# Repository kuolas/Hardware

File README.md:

# Hardware

Every folder is a board originally designed for a particular project but are generic enough to be used in other projects.

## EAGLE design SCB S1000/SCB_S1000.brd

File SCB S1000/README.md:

# SCB S1000

Stepper Controller Board based on L297 and L296.

These file were created using EAGLE 5.10

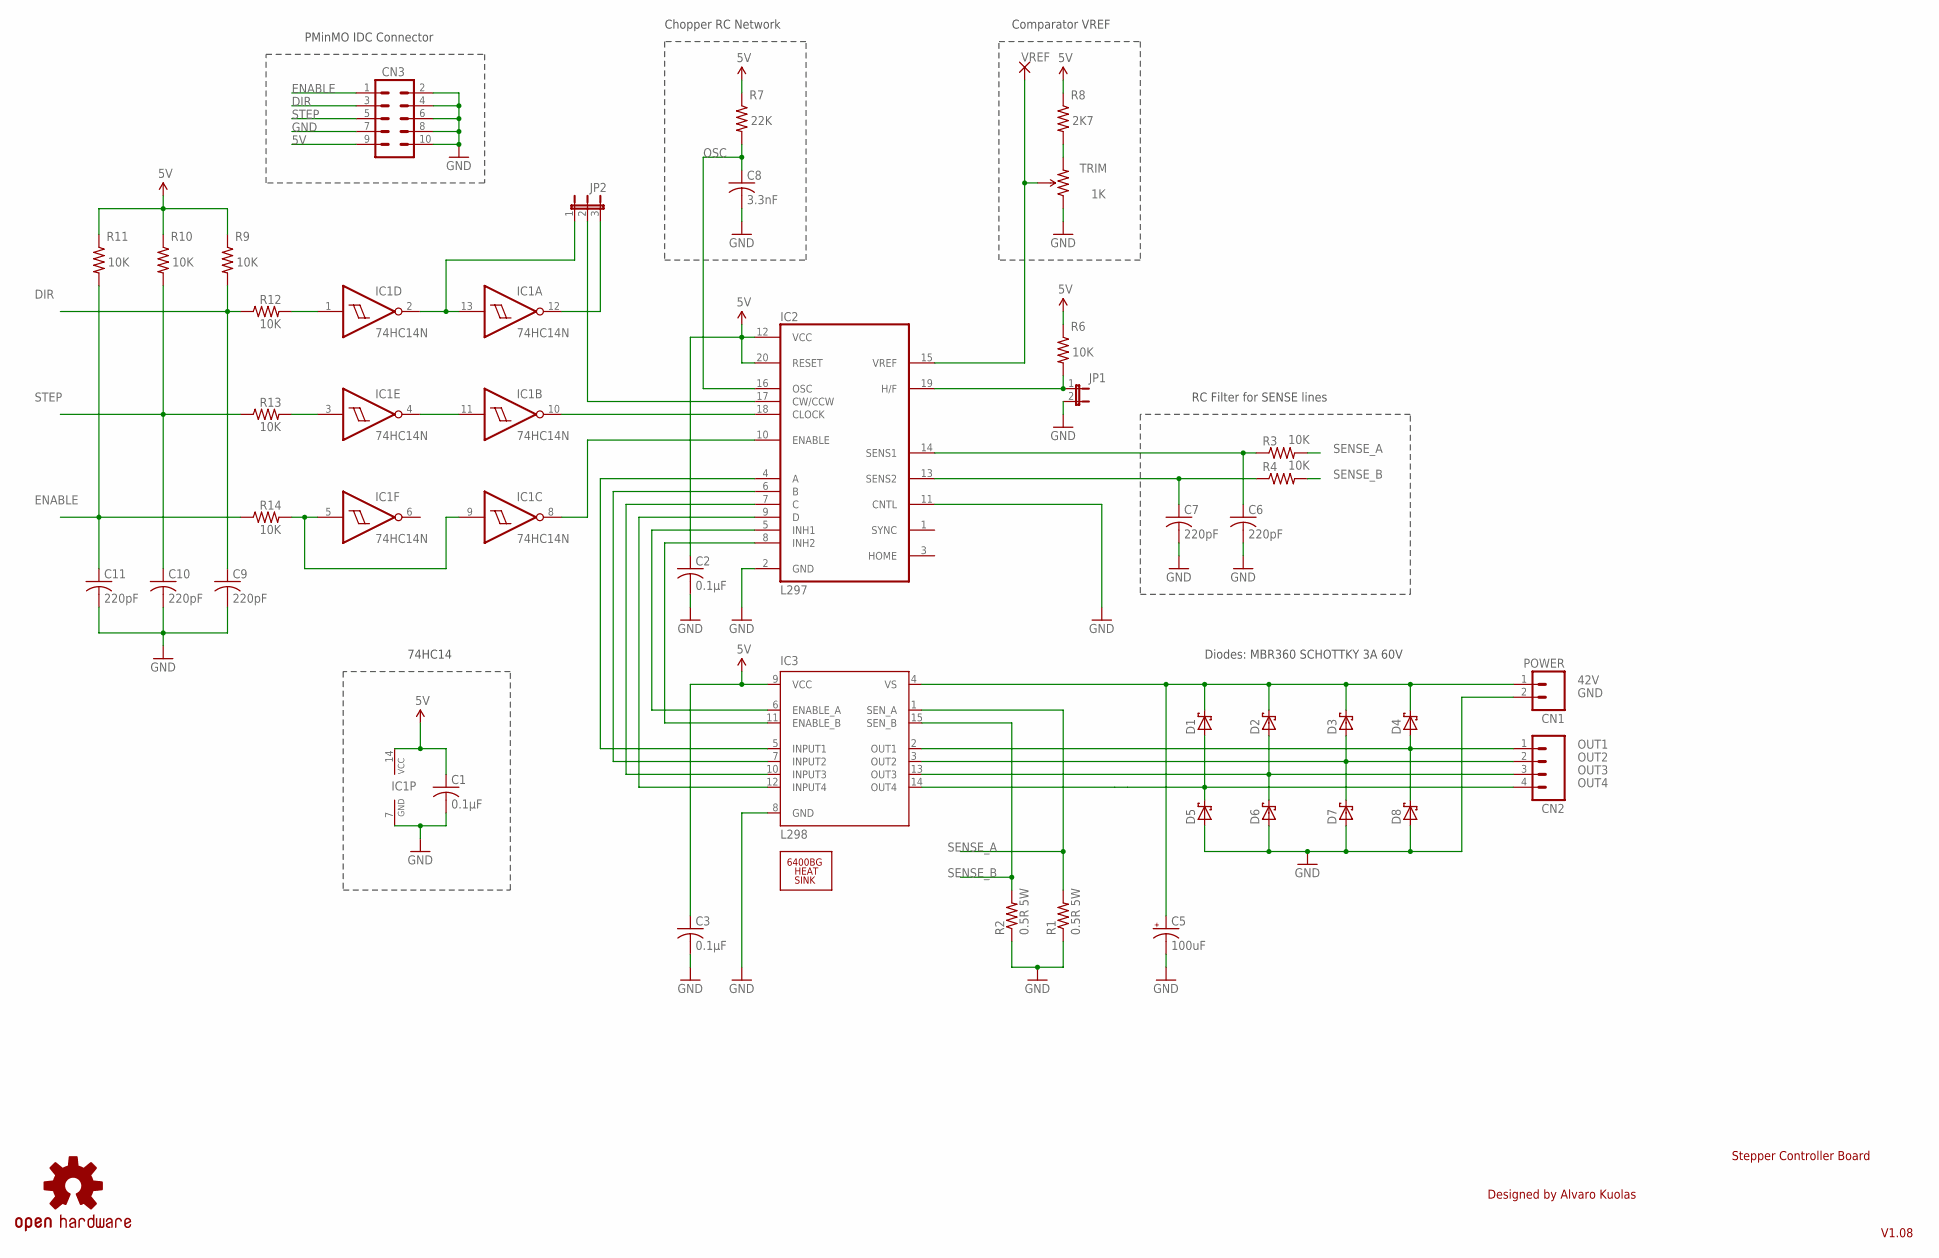
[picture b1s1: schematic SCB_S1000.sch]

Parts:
C1, C2, C3: 0.1µF; C050-024X044
C5: 100uF; E5-10,5
C6, C7, C9, C10, C11: 220pF; C050-024X044
C8: 3.3nF; C050-024X044
CN1: POWER; SCREWTERMINAL-3.5MM-2
CN2: STEPPER; SCREWTERMINAL-3.5MM-4
CN3: M05X2SHD; 2X5-SHROUDED
D1, D2, D3, D4, D5, D6, D7, D8: MBR360; DO201T15
IC1: 74HC14N; DIL14
IC2: L297; DIL20
IC3: L298; MULTIWATT-15
JP1: H/F; 1X02
JP2: DIR; 1X03
R1, R2: 0.5R 5W; 0922/22
R3, R4, R6, R9, R10, R11, R12, R13, R14: 10K; 0204/5
R7: 22K; 0204/5
R8: 2K7; 0204/5
TRIM: 1K; 3362U-2
U$2: 6400BG_HEATSINK
U$9: OSHW-LOGOL; OSHW-LOGO-L
VREF: VREF; 1,6/0,9

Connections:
5V: C1.1, C2.1, C3.1, CN3.9, IC1.14 (VCC), IC2.12 (VCC), IC2.20 (RESET), IC3.9 (VCC), R6.1, R7.1, R8.1, R9.1, R10.1, R11.1
42V: C5.+, CN1.1, D1.C, D2.C, D3.C, D4.C, IC3.4 (VS)
DIR: C9.1, CN3.3, R9.2, R12.1
ENABLE: C11.1, CN3.1, R11.2, R14.1
GND: C1.2, C2.2, C3.2, C5.-, C6.2, C7.2, C8.2, C9.2, C10.2, C11.2, CN1.2, CN3.2, CN3.4, CN3.6, CN3.7, CN3.8, CN3.10, D5.A, D6.A, D7.A, D8.A, IC1.7 (GND), IC2.2 (GND), IC2.11 (CNTL), IC3.8 (GND), JP1.2, R1.1, R2.1, TRIM.1 (CCW)
unnamed: IC2.4 (A), IC3.5 (INPUT1)
unnamed: IC2.6 (B), IC3.7 (INPUT2)
unnamed: IC2.19 (H/F), JP1.1, R6.2
unnamed: IC2.5 (INH1), IC3.6 (ENABLE_A)
unnamed: C7.1, IC2.13 (SENS2), R4.1
unnamed: IC2.7 (C), IC3.10 (INPUT3)
unnamed: IC2.9 (D), IC3.12 (INPUT4)
unnamed: IC2.8 (INH2), IC3.11 (ENABLE_B)
unnamed: C6.1, IC2.14 (SENS1), R3.1
unnamed: R8.2, TRIM.3 (CW)
unnamed: IC1.8 (O), IC2.10 (ENABLE)
unnamed: IC1.10 (O), IC2.18 (CLOCK)
unnamed: IC2.17 (CW/CCW), JP2.2
unnamed: IC1.3 (I), R13.2
unnamed: IC1.4 (O), IC1.11 (I)
unnamed: IC1.5 (I), IC1.9 (I), R14.2
unnamed: IC1.1 (I), R12.2
unnamed: IC1.2 (O), IC1.13 (I), JP2.1
unnamed: IC1.12 (O), JP2.3
OSC: C8.1, IC2.16 (OSC), R7.2
OUT1: CN2.1, D4.A, D8.C, IC3.2 (OUT1)
OUT2: CN2.2, D3.A, D7.C, IC3.3 (OUT2)
OUT3: CN2.3, D2.A, D6.C, IC3.13 (OUT3)
OUT4: CN2.4, D1.A, D5.C, IC3.14 (OUT4)
SENSE_A: IC3.1 (SEN_A), R1.2, R3.2
SENSE_B: IC3.15 (SEN_B), R2.2, R4.2
STEP: C10.1, CN3.5, R10.2, R13.1
VREF: IC2.15 (VREF), TRIM.2 (WIPER), VREF.1

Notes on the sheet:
Diodes: MBR360 SCHOTTKY 3A 60V
Stepper Controller Board
Chopper RC Network
PMinMO IDC Connector
RC Filter for SENSE lines
Comparator VREF
74HC14
V1.08
Designed by Alvaro Kuolas

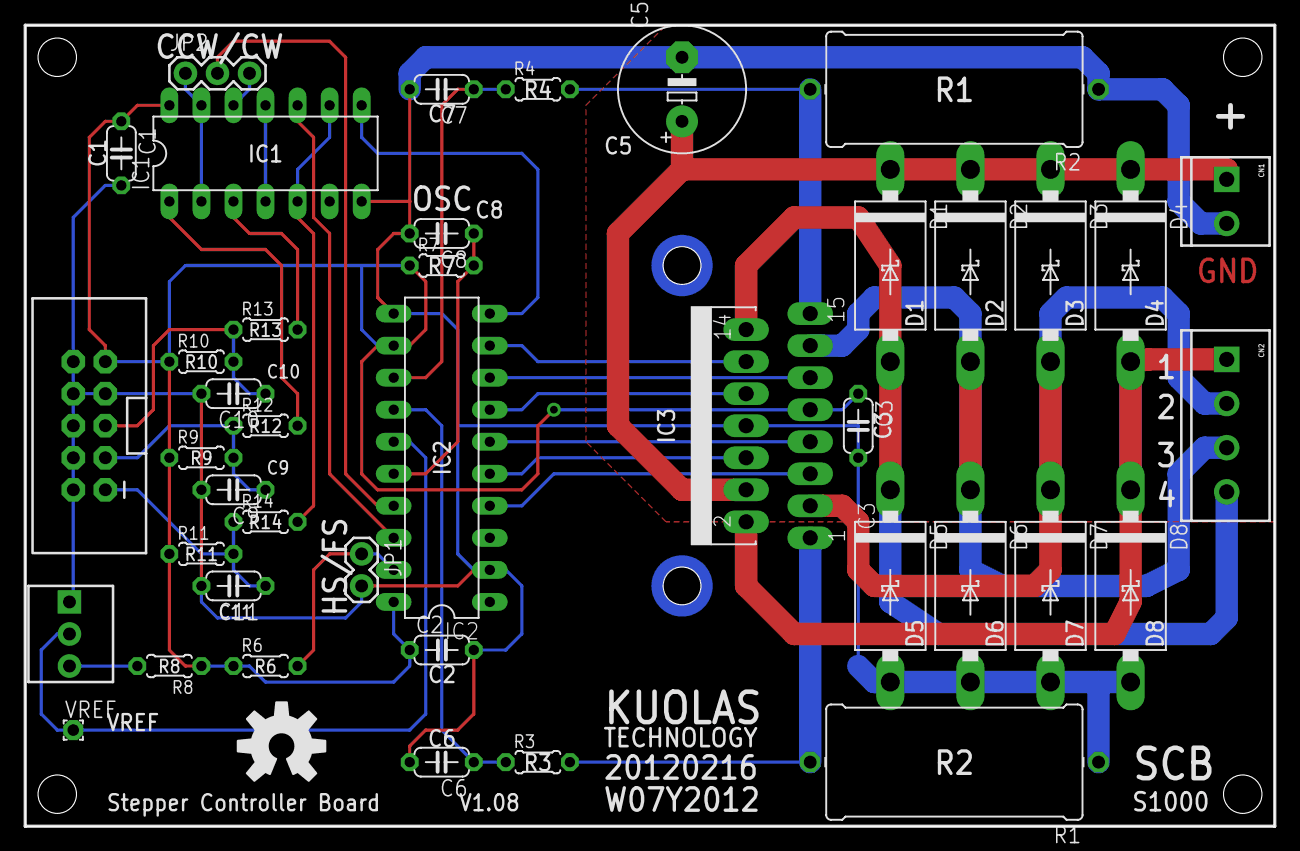
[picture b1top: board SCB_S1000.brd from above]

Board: 2 copper layers, 99.1 x 63.5 mm, 43 parts (0 on the bottom side), 33 nets.

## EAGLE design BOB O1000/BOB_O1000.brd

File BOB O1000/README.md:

# BOB O1000 

Break out Board intended to be used on a Desktop CNC.

The files were created using EAGLE 5.10

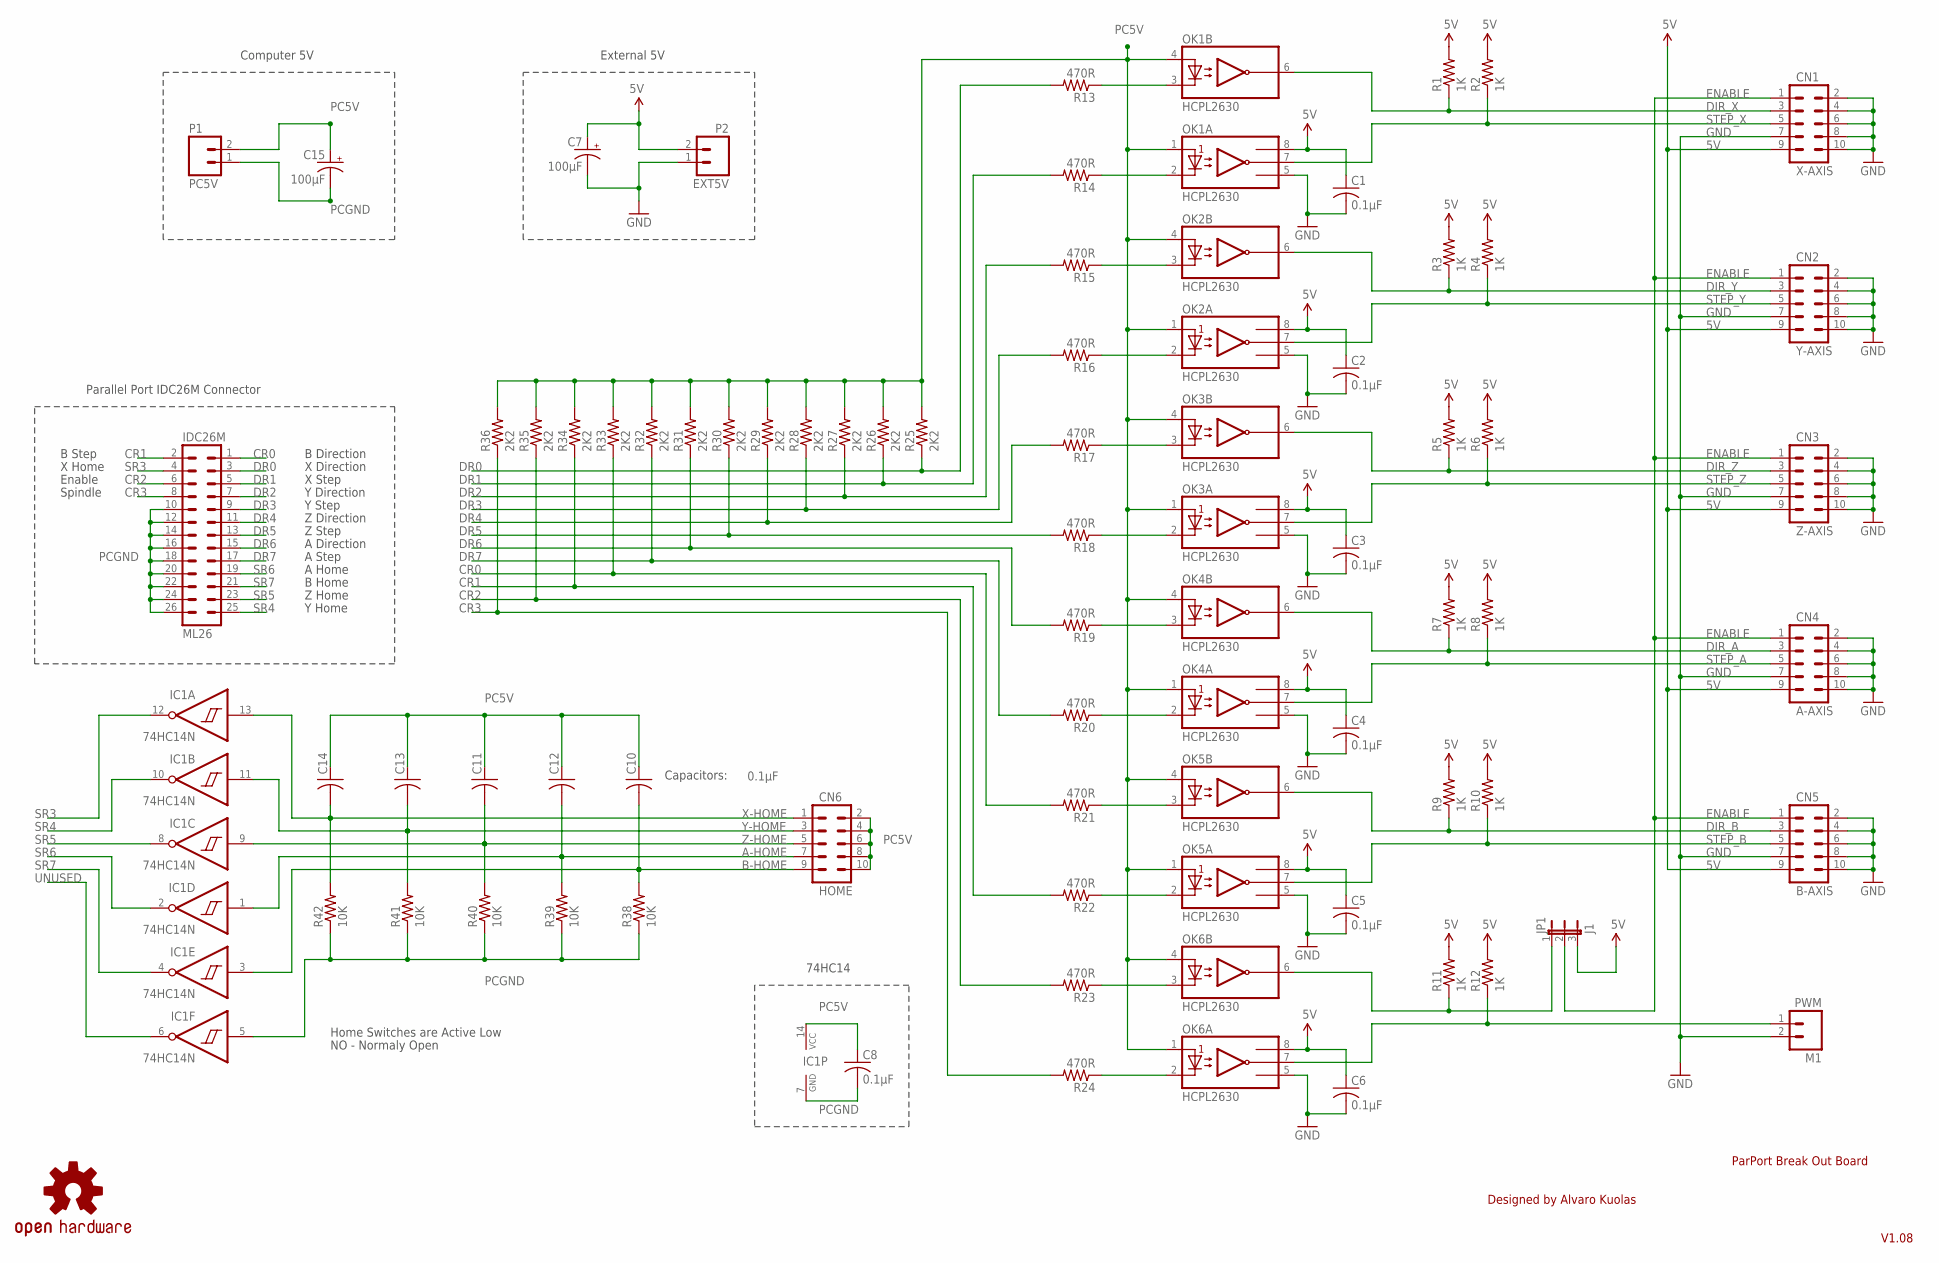
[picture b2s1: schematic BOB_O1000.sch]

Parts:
C1, C2, C3, C4, C5, C6, C8, C10, C11, C12, C13, C14: 0.1µF; C050-024X044
C7, C15: 100µF; E5-10,5
CN1: X-AXIS; 2X5-SHROUDED
CN2: Y-AXIS; 2X5-SHROUDED
CN3: Z-AXIS; 2X5-SHROUDED
CN4: A-AXIS; 2X5-SHROUDED
CN5: B-AXIS; 2X5-SHROUDED
CN6: HOME; 2X5-SHROUDED
IC1: 74HC14N; DIL14
JP1: J1; 1X03
M1: PWM; 1X02
ML26: IDC26M; ML26
OK1, OK2, OK3, OK4, OK5, OK6: HCPL2630; DIL08
P1: PC5V; SCREWTERMINAL-3.5MM-2
P2: EXT5V; SCREWTERMINAL-3.5MM-2
R1, R2, R3, R4, R5, R6, R7, R8, R9, R10, R11, R12: 1K; 0204/5
R13, R14, R15, R16, R17, R18, R19, R20, R21, R22, R23, R24: 470R; 0204/5
R25, R26, R27, R28, R29, R30, R31, R32, R33, R34, R35, R36: 2K2; 0204/5
R38, R39, R40, R41, R42: 10K; 0204/5
U$24: OSHW-LOGOL; OSHW-LOGO-L

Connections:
5V: C1.1, C2.1, C3.1, C4.1, C5.1, C6.1, C7.+, CN1.9, CN2.9, CN3.9, CN4.9, CN5.9, JP1.3, OK1.8 (VCC), OK2.8 (VCC), OK3.8 (VCC), OK4.8 (VCC), OK5.8 (VCC), OK6.8 (VCC), P2.2, R1.2, R2.2, R3.2, R4.2, R5.2, R6.2, R7.2, R8.2, R9.2, R10.2, R11.2, R12.2
A-HOME: C12.2, CN6.7, IC1.1 (I), R39.2
B-HOME: C10.2, CN6.9, IC1.3 (I), R38.2
CR0: ML26.1, R21.2, R33.1
CR1: ML26.2, R22.2, R34.1
CR2: ML26.6, R23.2, R35.1
CR3: ML26.8, R24.2, R36.1
DIR_A: CN4.3, OK4.6 (VO2), R7.1
DIR_B: CN5.3, OK5.6 (VO2), R9.1
DIR_X: CN1.3, OK1.6 (VO2), R1.1
DIR_Y: CN2.3, OK2.6 (VO2), R3.1
DIR_Z: CN3.3, OK3.6 (VO2), R5.1
DR0: ML26.3, R13.2, R25.1
DR1: ML26.5, R14.2, R26.1
DR2: ML26.7, R15.2, R27.1
DR3: ML26.9, R16.2, R28.1
DR4: ML26.11, R17.2, R29.1
DR5: ML26.13, R18.2, R30.1
DR6: ML26.15, R19.2, R31.1
DR7: ML26.17, R20.2, R32.1
ENABLE: CN1.1, CN2.1, CN3.1, CN4.1, CN5.1, JP1.2
GND: C1.2, C2.2, C3.2, C4.2, C5.2, C6.2, C7.-, CN1.2, CN1.4, CN1.6, CN1.7, CN1.8, CN1.10, CN2.2, CN2.4, CN2.6, CN2.7, CN2.8, CN2.10, CN3.2, CN3.4, CN3.6, CN3.7, CN3.8, CN3.10, CN4.2, CN4.4, CN4.6, CN4.7, CN4.8, CN4.10, CN5.2, CN5.4, CN5.6, CN5.7, CN5.8, CN5.10, M1.2, OK1.5 (GND), OK2.5 (GND), OK3.5 (GND), OK4.5 (GND), OK5.5 (GND), OK6.5 (GND), P2.1
unnamed: OK6.2 (C1), R24.1
unnamed: JP1.1, OK6.6 (VO2), R11.1
unnamed: M1.1, OK6.7 (VO1), R12.1
unnamed: OK6.3 (C2), R23.1
unnamed: OK1.2 (C1), R14.1
unnamed: OK1.3 (C2), R13.1
unnamed: OK2.3 (C2), R15.1
unnamed: OK2.2 (C1), R16.1
unnamed: OK3.3 (C2), R17.1
unnamed: OK3.2 (C1), R18.1
unnamed: OK4.3 (C2), R19.1
unnamed: OK4.2 (C1), R20.1
unnamed: OK5.3 (C2), R21.1
unnamed: OK5.2 (C1), R22.1
PC5V: C8.1, C10.1, C11.1, C12.1, C13.1, C14.1, C15.+, CN6.2, CN6.4, CN6.6, CN6.8, CN6.10, IC1.14 (VCC), OK1.1 (A1), OK1.4 (A2), OK2.1 (A1), OK2.4 (A2), OK3.1 (A1), OK3.4 (A2), OK4.1 (A1), OK4.4 (A2), OK5.1 (A1), OK5.4 (A2), OK6.1 (A1), OK6.4 (A2), P1.2, R25.2, R26.2, R27.2, R28.2, R29.2, R30.2, R31.2, R32.2, R33.2, R34.2, R35.2, R36.2
PCGND: C8.2, C15.-, IC1.5 (I), IC1.7 (GND), ML26.10, ML26.12, ML26.14, ML26.16, ML26.18, ML26.20, ML26.22, ML26.24, ML26.26, P1.1, R38.1, R39.1, R40.1, R41.1, R42.1
SR3: IC1.12 (O), ML26.4
SR4: IC1.10 (O), ML26.25
SR5: IC1.8 (O), ML26.23
SR6: IC1.2 (O), ML26.19
SR7: IC1.4 (O), ML26.21
STEP_A: CN4.5, OK4.7 (VO1), R8.1
STEP_B: CN5.5, OK5.7 (VO1), R10.1
STEP_X: CN1.5, OK1.7 (VO1), R2.1
STEP_Y: CN2.5, OK2.7 (VO1), R4.1
STEP_Z: CN3.5, OK3.7 (VO1), R6.1
UNUSED: IC1.6 (O)
X-HOME: C14.2, CN6.1, IC1.13 (I), R42.2
Y-HOME: C13.2, CN6.3, IC1.11 (I), R41.2
Z-HOME: C11.2, CN6.5, IC1.9 (I), R40.2

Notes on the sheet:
V1.08
ParPort Break Out Board
External 5V
Computer 5V
X Direction
Y Direction
Z Direction
A Direction
B Direction
Enable
Spindle
X Step
Y Step
Z Step
A Step
B Step
74HC14
Parallel Port IDC26M Connector
X Home
Y Home
Z Home
B Home
A Home
Designed by Alvaro Kuolas
Capacitors:
Home Switches are Active Low
NO - Normaly Open

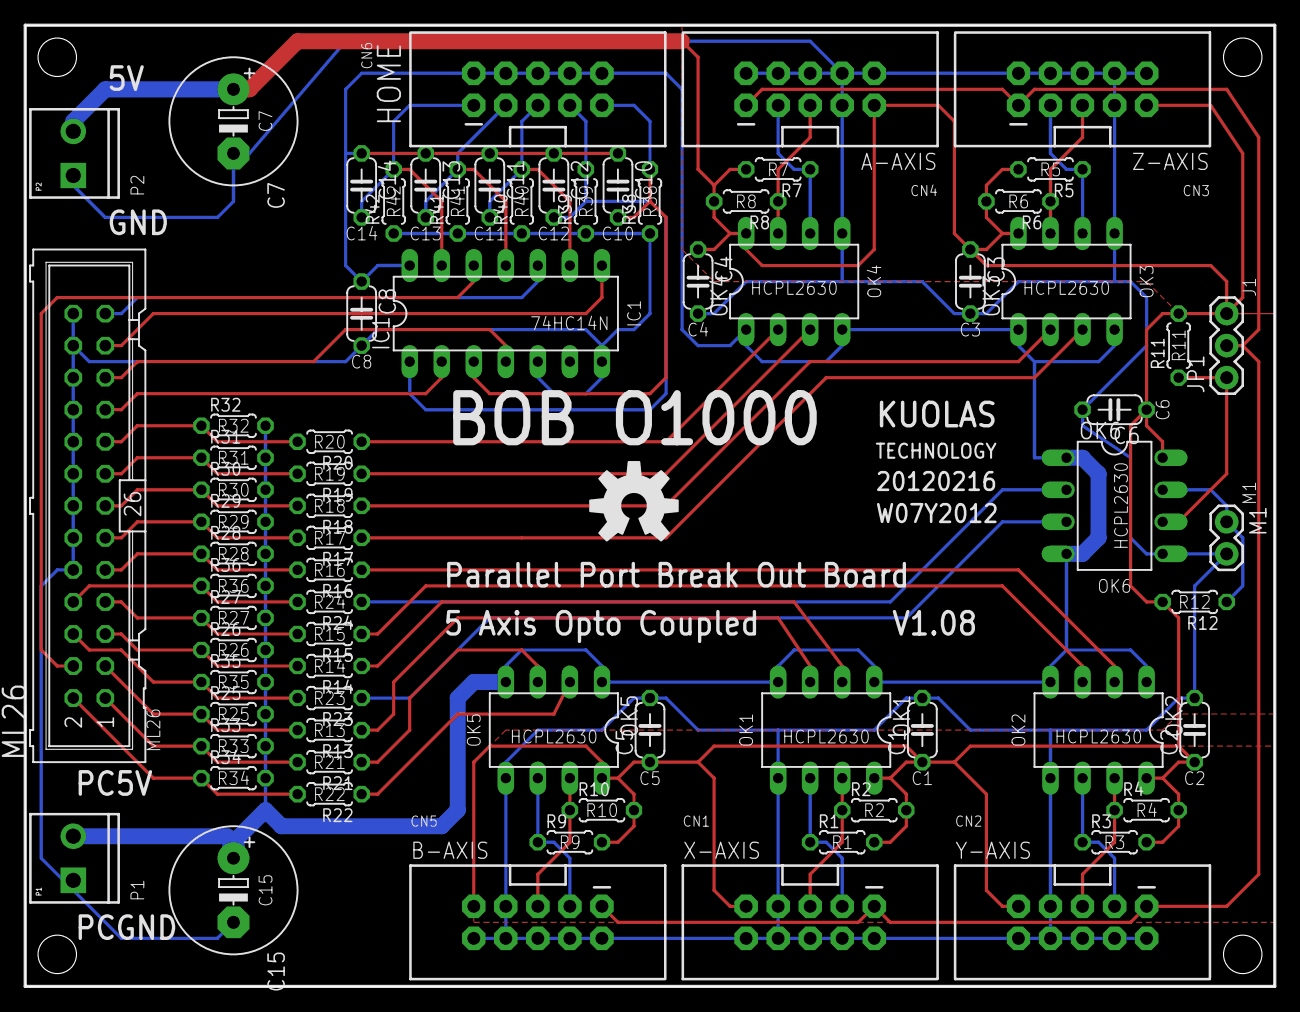
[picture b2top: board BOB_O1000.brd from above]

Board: 2 copper layers, 99.1 x 76.2 mm, 74 parts (0 on the bottom side), 51 nets.

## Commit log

2018-09-29 Initial Version
